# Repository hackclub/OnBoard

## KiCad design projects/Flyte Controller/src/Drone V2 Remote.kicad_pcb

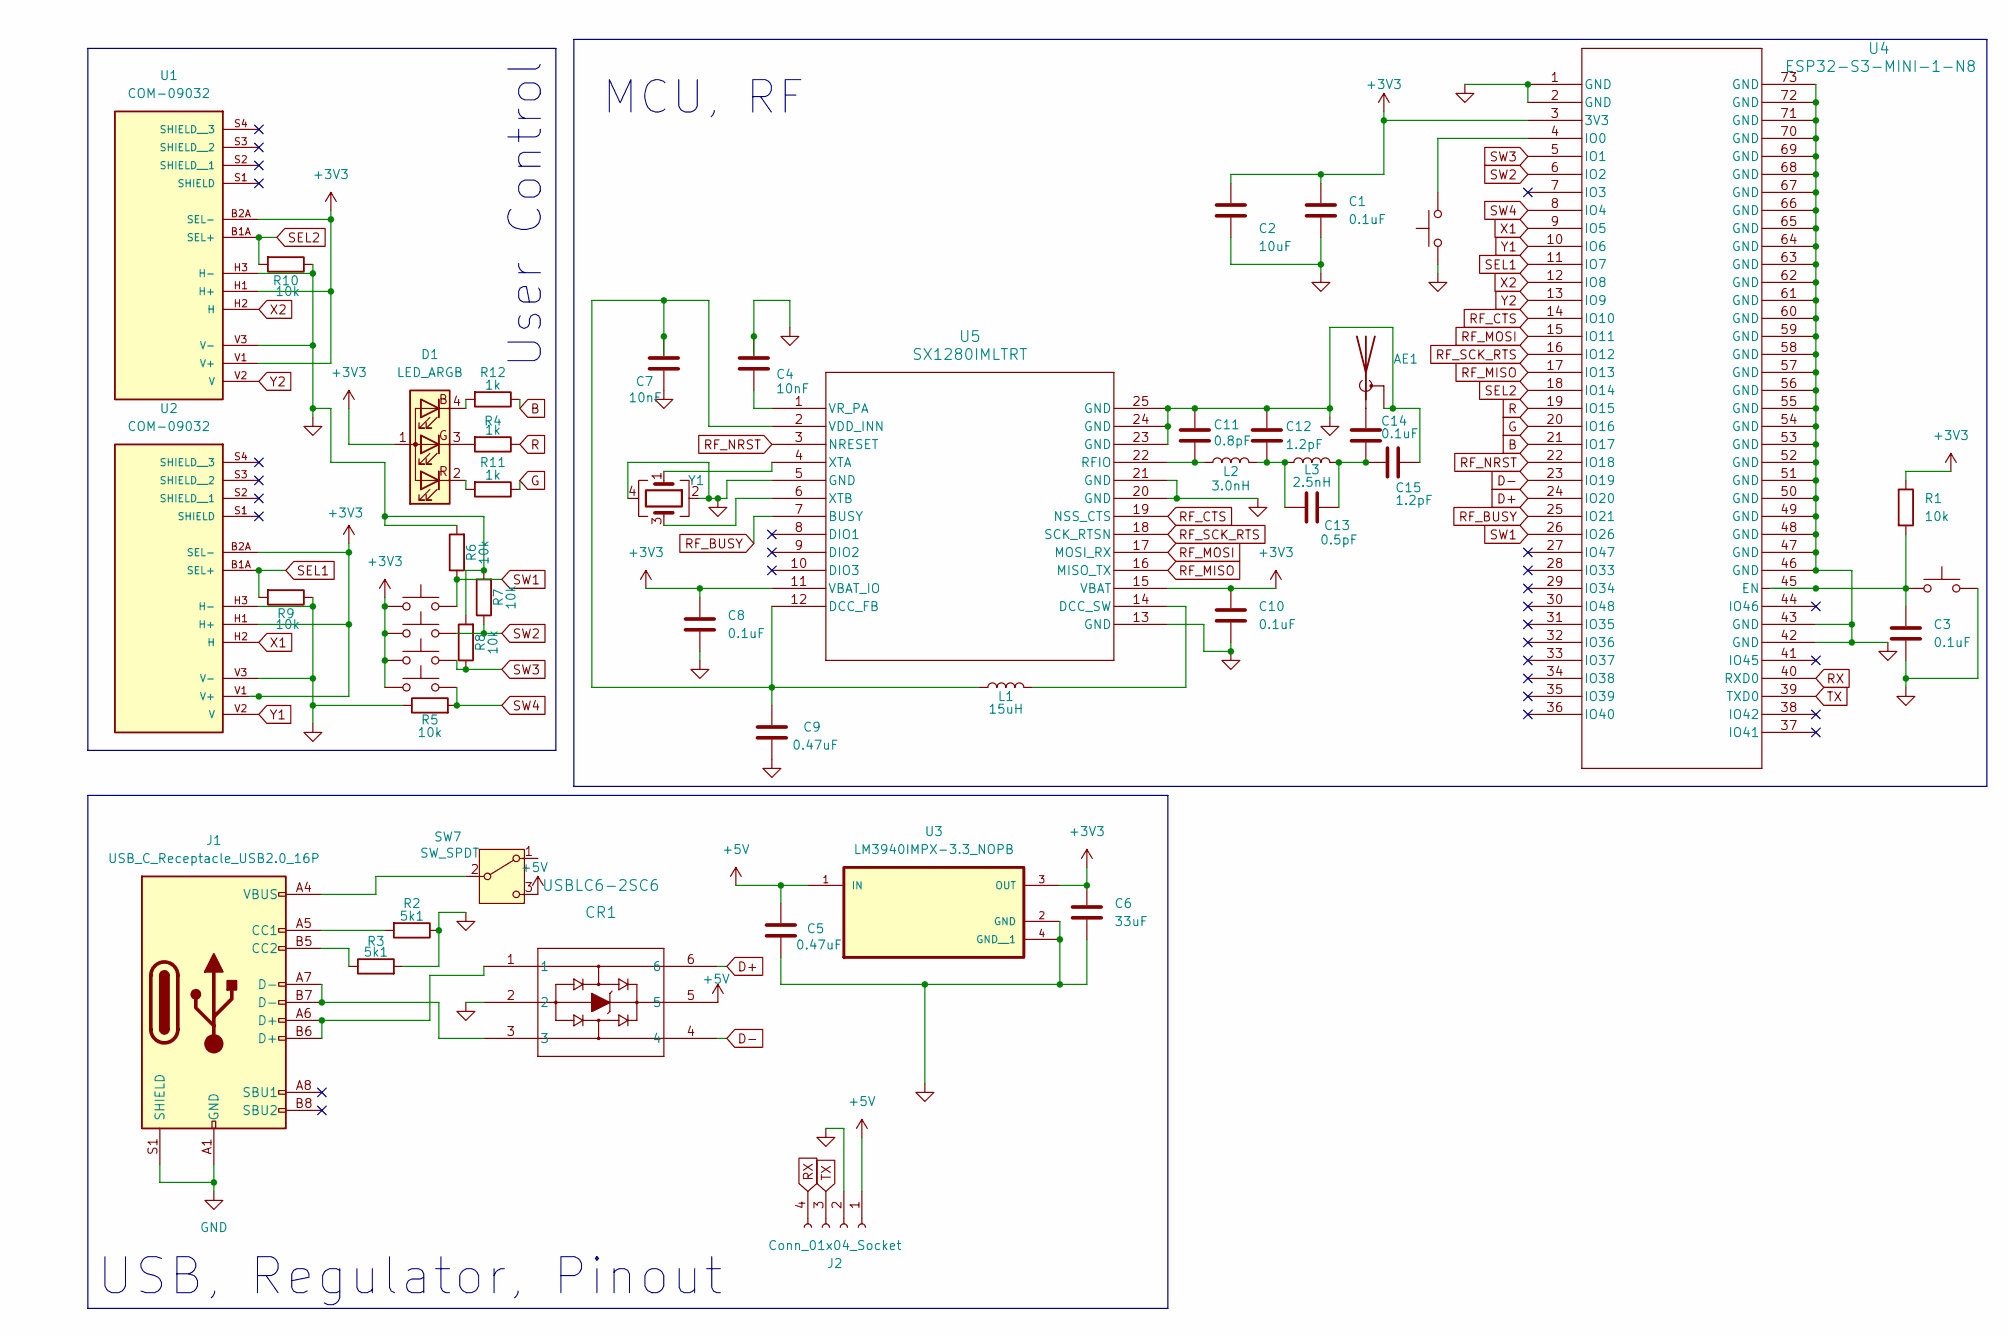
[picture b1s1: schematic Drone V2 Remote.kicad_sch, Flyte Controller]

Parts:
AE1: Antenna_Shield; CINCH_142-0701-801
C1, C3, C8, C10, C14: 0.1uF; CAPC0402X22N
C2: 10uF; CAPC1005X70N
C4, C7: 10nF; CAPC1005X70N
C5, C9: 0.47uF; CAP_CL05_SAM
C6: 33uF; CAP_C1005_TDK
C11: 0.8pF; G-155_MUR
C12, C15: 1.2pF; G-155_MUR
C13: 0.5pF; CAPC1005X55N
CR1: USBLC6-2SC6; SOT23-6L_STM
D1: LED_ARGB; LED_TATRGB_INL
J1: USB_C_Receptacle_USB2.0_16P; USB_C_Receptacle_GCT_USB4105-xx-A_16P_TopMnt_Horizontal
J2: Conn_01x04_Socket; PinHeader_1x04_P1.00mm_Horizontal
L1: 15uH; IND_2012_TDK
L2: 3.0nH; IND1005_LQW15_MUR
L3: 2.5nH; INDC1006X60N
R1, R5, R6, R7, R8, R9, R10: 10k; RC0402N_YAG
R2, R3: 5k1; RES_TNPW0402_VIS
R4, R11, R12: 1k; RC0402N_YAG
SW1, SW2, SW3, SW4: SW_Push; SW_PUSH_6mm_H4.3mm
SW5, SW6: SW_Push; SW_Tactile_SPST_NO_Straight_CK_PTS636Sx25SMTRLFS
SW7: SW_SPDT; SW_EG1218
U1, U2: COM-09032; XDCR_COM-09032; PARTREV N/A
U3: LM3940IMPX-3.3_NOPB; SOT230P700X180-4N
U4: ESP32-S3-MINI-1-N8; ESP32-S3-MINI-1_EXP
U5: SX1280IMLTRT; QFN24_4X4_SEM
Y1: FW520WFMT1; CRYSTAL_FW520WFMT1_DIO

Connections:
+3V3: C1.1, C2.1, C6.1, C8.1, C10.1, D1.1 (A), R1.1, SW1.1, SW2.1, SW3.1, SW4.1, U1.B2A (SEL-), U1.H1 (H+), U1.V1 (V+), U2.B2A (SEL-), U2.H1 (H+), U2.V1 (V+), U3.3 (OUT), U4.3 (3V3), U5.11 (VBAT_IO), U5.15 (VBAT)
+5V: C5.1, CR1.5, J2.1, SW7.3 (C), U3.1 (IN)
B: R12.1, U4.21 (IO17)
D+: CR1.6, U4.24 (IO20)
D-: CR1.4, U4.23 (IO19)
G: R11.1, U4.20 (IO16)
GND: AE1.2 (Shield), C1.2, C2.2, C3.2, C4.1, C5.2, C6.2, C7.2, C8.2, C9.2, C10.2, C11.1, C12.1, C15.1, CR1.2, J1.A1 (GND), J1.A12 (GND), J1.B1 (GND), J1.B12 (GND), J1.S1 (SHIELD), J2.2, R2.1, R3.2, R5.1, R6.2, R7.2, R8.2, R9.1, R10.1, SW5.2, SW6.1, U1.H3 (H-), U1.V3 (V-), U2.H3 (H-), U2.V3 (V-), U3.2 (GND), U3.4 (GND__1), U4.1 (GND), U4.2 (GND), U4.42 (GND), U4.43 (GND), U4.46 (GND), U4.47 (GND), U4.48 (GND), U4.49 (GND), U4.50 (GND), U4.51 (GND), U4.52 (GND), U4.53 (GND), U4.54 (GND), U4.55 (GND), U4.56 (GND), U4.57 (GND), U4.58 (GND), U4.59 (GND), U4.60 (GND), U4.61 (GND), U4.62 (GND), U4.63 (GND), U4.64 (GND), U4.65 (GND), U4.66 (GND), U4.67 (GND), U4.68 (GND), U4.69 (GND), U4.70 (GND), U4.71 (GND), U4.72 (GND), U4.73 (GND), U5.5 (GND), U5.13 (GND), U5.20 (GND), U5.21 (GND), U5.23 (GND), U5.24 (GND), U5.25 (GND), Y1.2, Y1.4
unnamed: AE1.1 (A), C14.1
unnamed: C12.2, C13.1, L2.2, L3.1
unnamed: C13.2, C14.2, C15.2, L3.2
unnamed: CR1.1, J1.A6 (D+), J1.B6 (D+)
unnamed: CR1.3, J1.A7 (D-), J1.B7 (D-)
unnamed: D1.4 (BK), R12.2
unnamed: D1.3 (GK), R4.2
unnamed: D1.2 (RK), R11.2
unnamed: J1.A5 (CC1), R2.2
unnamed: J1.B5 (CC2), R3.1
unnamed: J1.A4 (VBUS), J1.A9 (VBUS), J1.B4 (VBUS), J1.B9 (VBUS), SW7.2 (B)
unnamed: C3.1, R1.2, SW5.1, U4.45 (EN)
unnamed: SW6.2, U4.4 (IO0)
unnamed: C7.1, C9.1, L1.1, U5.2 (VDD_INN), U5.12 (DCC_FB)
unnamed: L1.2, U5.14 (DCC_SW)
unnamed: C11.2, L2.1, U5.22 (RFIO)
unnamed: C4.2, U5.1 (VR_PA)
unnamed: U5.4 (XTA), Y1.1
unnamed: U5.6 (XTB), Y1.3
R: R4.1, U4.19 (IO15)
RF_BUSY: U4.25 (IO21), U5.7 (BUSY)
RF_CTS: U4.14 (IO10), U5.19 (NSS_CTS)
RF_MISO: U4.17 (IO13), U5.16 (MISO_TX)
RF_MOSI: U4.15 (IO11), U5.17 (MOSI_RX)
RF_NRST: U4.22 (IO18), U5.3 (NRESET)
RF_SCK_RTS: U4.16 (IO12), U5.18 (SCK_RTSN)
RX: J2.4, U4.40 (RXD0)
SEL1: R9.2, U2.B1A (SEL+), U4.11 (IO7)
SEL2: R10.2, U1.B1A (SEL+), U4.18 (IO14)
SW1: R6.1, SW1.2, U4.26 (IO26)
SW2: R7.1, SW2.2, U4.6 (IO2)
SW3: R8.1, SW3.2, U4.5 (IO1)
SW4: R5.2, SW4.2, U4.8 (IO4)
TX: J2.3, U4.39 (TXD0)
X1: U2.H2 (H), U4.9 (IO5)
X2: U1.H2 (H), U4.12 (IO8)
Y1: U2.V2 (V), U4.10 (IO6)
Y2: U1.V2 (V), U4.13 (IO9)

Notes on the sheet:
User Control
MCU, RF
USB, Regulator, Pinout

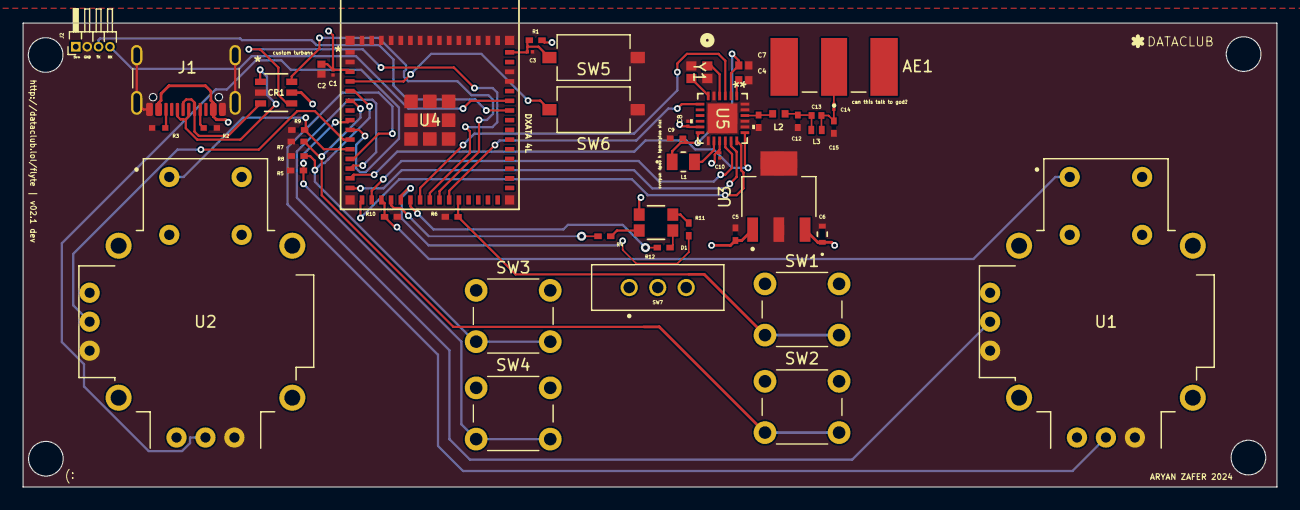
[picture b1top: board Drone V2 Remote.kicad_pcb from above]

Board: 4 copper layers, 110.0 x 40.7 mm, 48 parts (0 on the bottom side), 45 nets.

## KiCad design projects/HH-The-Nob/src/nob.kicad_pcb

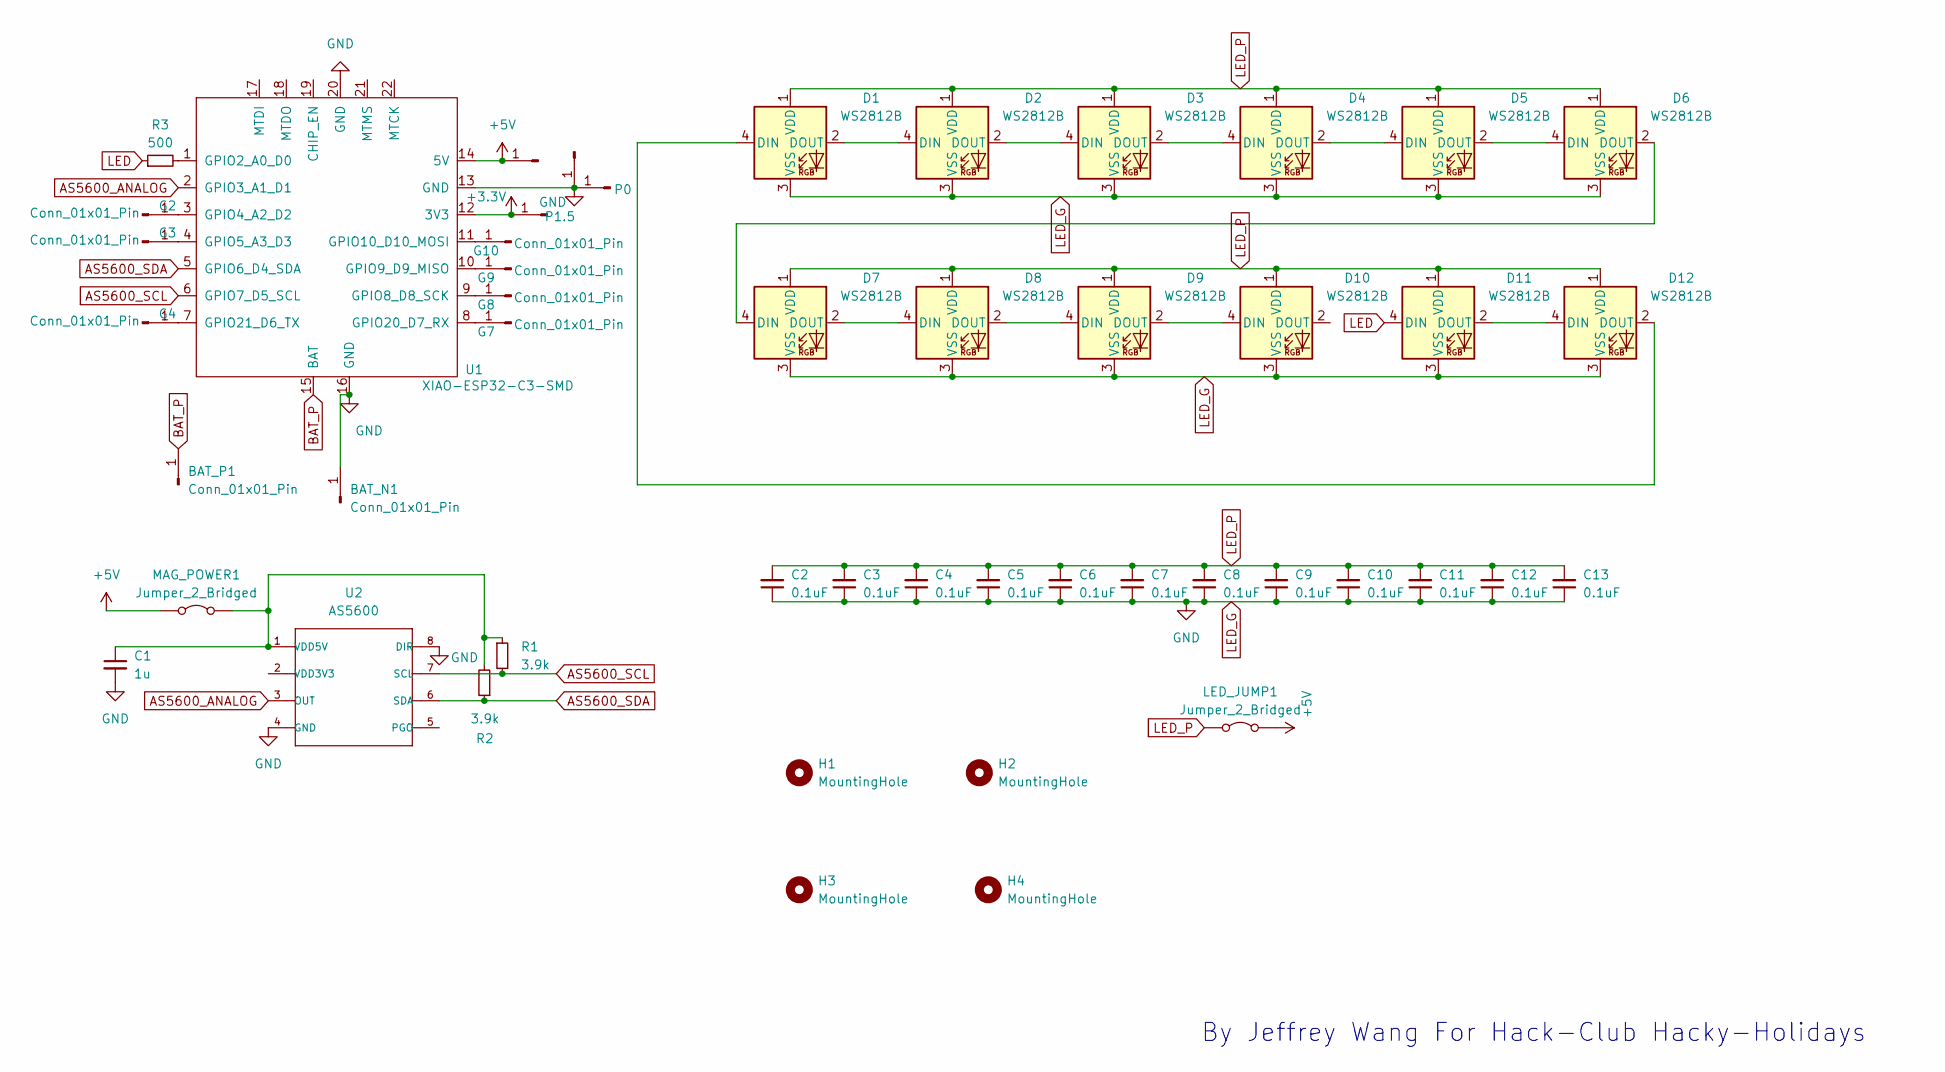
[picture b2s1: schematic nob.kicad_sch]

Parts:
BAT_N1: Conn_01x01_Pin; SolderWire-0.5sqmm_1x01_D0.9mm_OD2.1mm
BAT_P1: Conn_01x01_Pin; SolderWire-0.5sqmm_1x01_D0.9mm_OD2.1mm
C1: 1u; C_0603_1608Metric; LCSC C15849
C2, C3, C4, C5, C6, C7, C8, C9, C10, C11, C12, C13: 0.1uF; C_0805_2012Metric; LCSC C49678
D1, D2, D3, D4, D5, D6, D7, D8, D9, D10, D11, D12: WS2812B; LED_WS2812B_PLCC4_5.0x5.0mm_P3.2mm; LCSC C114586
G2, G3, G4, G7, G8, G9, G10: Conn_01x01_Pin; SolderWire-0.1sqmm_1x01_D0.4mm_OD1mm
H1, H2, H3, H4: MountingHole; MountingHole_3.2mm_M3_DIN965_Pad_TopBottom
LED_JUMP1: Jumper_2_Bridged; SolderJumper-2_P1.3mm_Bridged2Bar_Pad1.0x1.5mm
MAG_POWER1: Jumper_2_Bridged; SolderJumper-2_P1.3mm_Bridged2Bar_Pad1.0x1.5mm
P0, P1, P1.5, P10: Conn_01x01_Pin; SolderWire-0.1sqmm_1x01_D0.4mm_OD1mm
R1, R2: 3.9k; R_0805_2012Metric; LCSC C17614
R3: 500; C_0805_2012Metric; LCSC C17408
U1: XIAO-ESP32-C3-SMD; XIAO-ESP32C3-SMD
U2: AS5600; LCSC C499458

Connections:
+3.3V: P1.5.1, U1.12 (3V3)
+5V: LED_JUMP1.2 (B), MAG_POWER1.1 (A), P1.1, U1.14 (5V)
AS5600_ANALOG: U1.2 (GPIO3_A1_D1), U2.3 (OUT)
AS5600_SCL: R1.2, U1.6 (GPIO7_D5_SCL), U2.7 (SCL)
AS5600_SDA: R2.1, U1.5 (GPIO6_D4_SDA), U2.6 (SDA)
BAT_P: BAT_P1.1, U1.15 (BAT)
LED: D11.4 (DIN), R3.1
LED_G: BAT_N1.1, C1.2, C2.1, C3.1, C4.1, C5.1, C6.1, C7.1, C8.1, C9.1, C10.1, C11.1, C12.1, C13.1, D1.3 (VSS), D2.3 (VSS), D3.3 (VSS), D4.3 (VSS), D5.3 (VSS), D6.3 (VSS), D7.3 (VSS), D8.3 (VSS), D9.3 (VSS), D10.3 (VSS), D11.3 (VSS), D12.3 (VSS), P0.1, P10.1, U1.13 (GND), U1.16 (GND), U1.20 (GND), U2.4 (GND), U2.8 (DIR)
LED_P: C2.2, C3.2, C4.2, C5.2, C6.2, C7.2, C8.2, C9.2, C10.2, C11.2, C12.2, C13.2, D1.1 (VDD), D2.1 (VDD), D3.1 (VDD), D4.1 (VDD), D5.1 (VDD), D6.1 (VDD), D7.1 (VDD), D8.1 (VDD), D9.1 (VDD), D10.1 (VDD), D11.1 (VDD), D12.1 (VDD), LED_JUMP1.1 (A)
unnamed: D1.4 (DIN), D12.2 (DOUT)
unnamed: D1.2 (DOUT), D2.4 (DIN)
unnamed: D2.2 (DOUT), D3.4 (DIN)
unnamed: D3.2 (DOUT), D4.4 (DIN)
unnamed: D4.2 (DOUT), D5.4 (DIN)
unnamed: D5.2 (DOUT), D6.4 (DIN)
unnamed: D6.2 (DOUT), D7.4 (DIN)
unnamed: D7.2 (DOUT), D8.4 (DIN)
unnamed: D8.2 (DOUT), D9.4 (DIN)
unnamed: D9.2 (DOUT), D10.4 (DIN)
unnamed: D11.2 (DOUT), D12.4 (DIN)
unnamed: G2.1, U1.3 (GPIO4_A2_D2)
unnamed: G3.1, U1.4 (GPIO5_A3_D3)
unnamed: G4.1, U1.7 (GPIO21_D6_TX)
unnamed: G7.1, U1.8 (GPIO20_D7_RX)
unnamed: G8.1, U1.9 (GPIO8_D8_SCK)
unnamed: G9.1, U1.10 (GPIO9_D9_MISO)
unnamed: G10.1, U1.11 (GPIO10_D10_MOSI)
unnamed: C1.1, MAG_POWER1.2 (B), R1.1, R2.2, U2.1 (VDD5V)
unnamed: R3.2, U1.1 (GPIO2_A0_D0)

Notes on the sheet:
By Jeffrey Wang For Hack-Club Hacky-Holidays

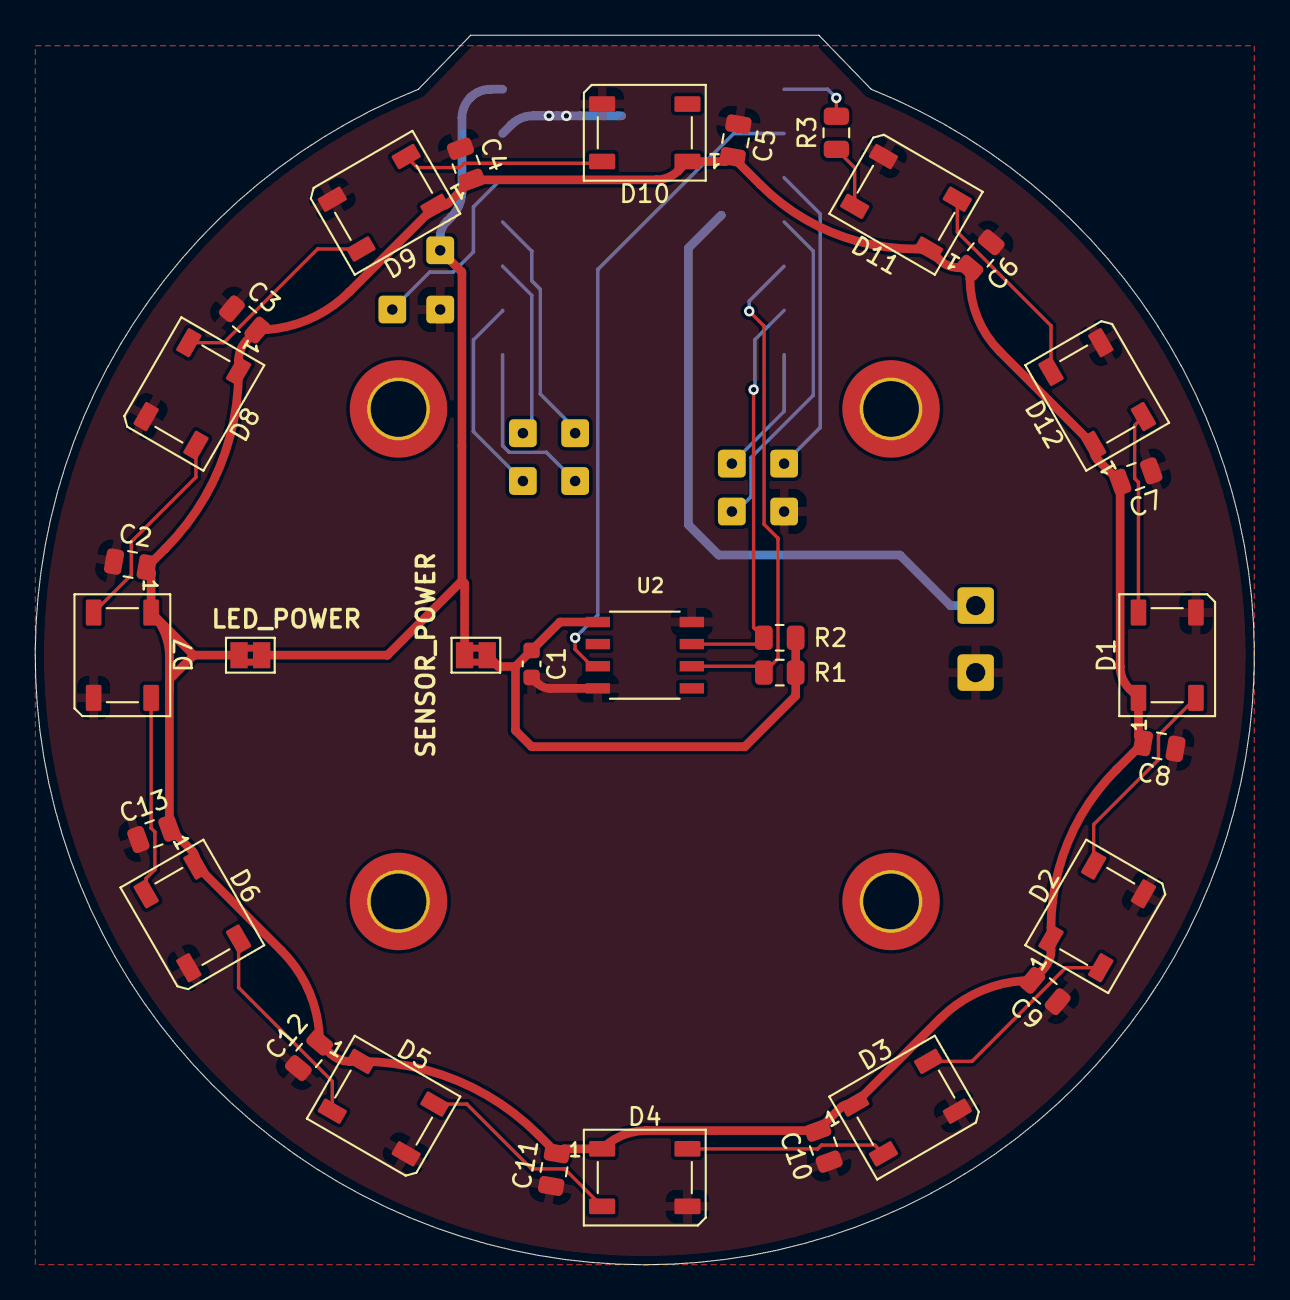
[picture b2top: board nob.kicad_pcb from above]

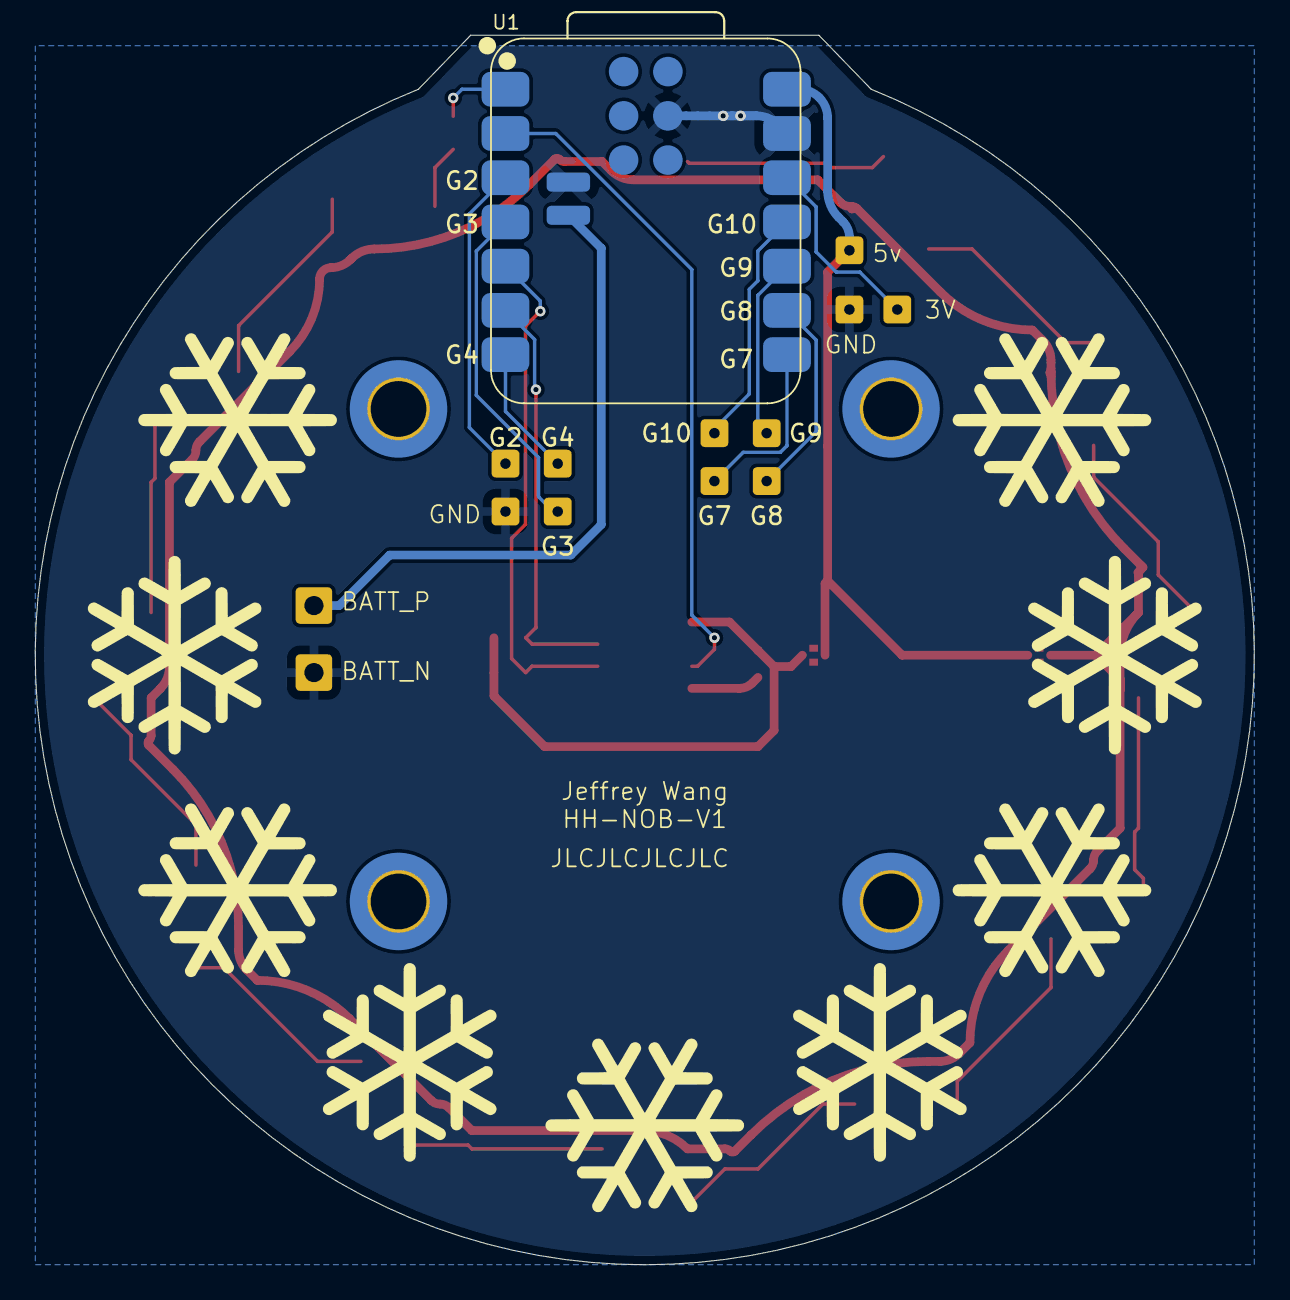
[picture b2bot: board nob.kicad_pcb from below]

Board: 2 copper layers, 70.0 x 70.6 mm, 49 parts (14 on the bottom side), 29 nets.

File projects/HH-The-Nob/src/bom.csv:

Designator,Footprint,Quantity,Value,LCSC Part #
"BAT_N1, BAT_P1",SolderWire-0.5sqmm_1x01_D0.9mm_OD2.1mm,2,Conn_01x01_Pin,
C1,0603,1,1u,C15849
"C10, C11, C12, C13, C2, C3, C4, C5, C6, C7, C8, C9",0805,12,0.1uF,C49678
"D1, D10, D11, D12, D2, D3, D4, D5, D6, D7, D8, D9",LED_WS2812B_PLCC4_5.0x5.0mm_P3.2mm,12,WS2812B,C114586
"G10, G2, G3, G4, G7, G8, G9, P0, P1, P1.5, P10",SolderWire-0.1sqmm_1x01_D0.4mm_OD1mm,11,Conn_01x01_Pin,
"LED_JUMP1, MAG_POWER1",SolderJumper-2_P1.3mm_Bridged2Bar_Pad1.0x1.5mm,2,Jumper_2_Bridged,
"R1, R2",0805,2,3.9k,C17614
R3,0805,1,500,C17408
U1,XIAO-ESP32C3-SMD,1,XIAO-ESP32-C3-SMD,
U2,AS5600,1,AS5600,C499458

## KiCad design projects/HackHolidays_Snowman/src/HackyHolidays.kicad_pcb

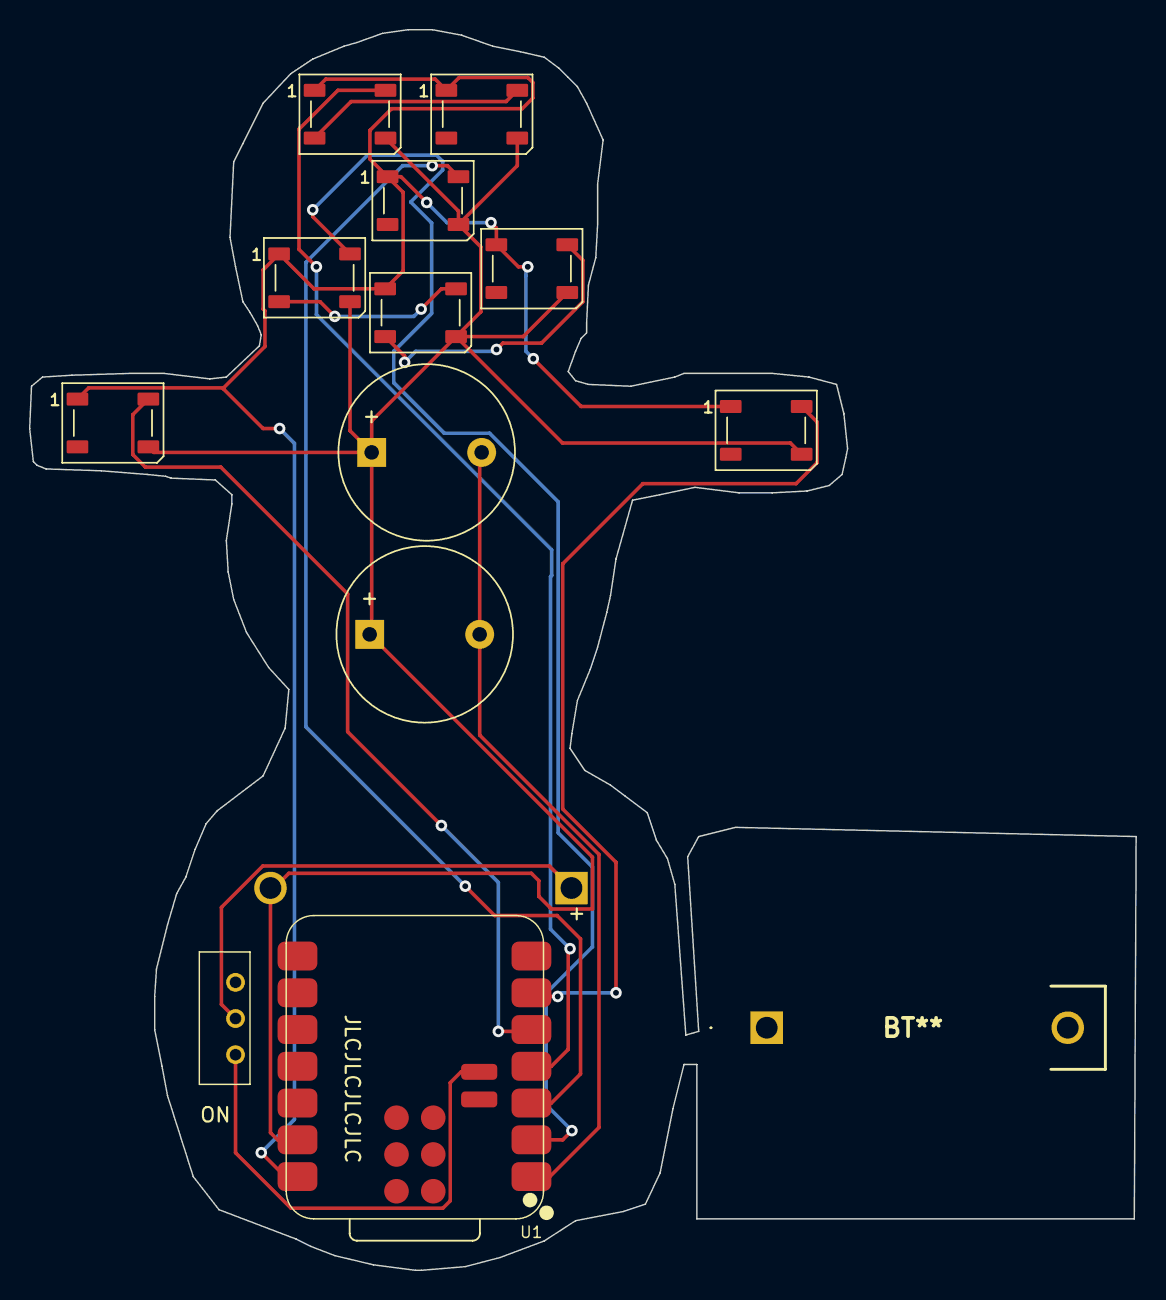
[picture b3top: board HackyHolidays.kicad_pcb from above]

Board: 2 copper layers, 76.5 x 85.7 mm, 14 parts (1 on the bottom side), 13 nets.

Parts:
BT1: BS-07-A1BJ001; K31260DL1
BT**: BS07A1BJ001
BZ1, BZ2: Buzzer; Buzzer_12x9.5RM7.6
D1, D2, D3, D8, D10, D11, D12, D13: WS2812B; LED_WS2812B_PLCC4_5.0x5.0mm_P3.2mm
S1: K3-1260D-L1; BS07A1BJ001
U1: XIAO-ESP32-C3-SMD; XIAO-ESP32C3-SMD

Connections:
+5V: D1.1 (VDD), D2.1 (VDD), D3.1 (VDD), D8.1 (VDD), D10.1 (VDD), D11.1 (VDD), D12.1 (VDD), D13.1 (VDD), U1.14 (5V)
GND: BZ1.1 (+), BZ2.1 (+), D1.3 (VSS), D2.3 (VSS), D3.3 (VSS), D8.3 (VSS), D10.3 (VSS), D11.3 (VSS), D12.3 (VSS), D13.3 (VSS), S1.2, U1.13 (GND)
unnamed: BT1.1 (+), U1.15 (BAT)
unnamed: BT1.2 (-), S1.1
unnamed: BZ1.2 (-), BZ2.2 (-), U1.1 (GPIO2_A0_D0)
unnamed: D1.4 (DIN), U1.3 (GPIO4_A2_D2)
unnamed: D2.4 (DIN), D8.2 (DOUT)
unnamed: D2.2 (DOUT), D3.4 (DIN)
unnamed: D8.4 (DIN), U1.2 (GPIO3_A1_D1)
unnamed: D10.4 (DIN), U1.4 (GPIO5_A3_D3)
unnamed: D10.2 (DOUT), D11.4 (DIN)
unnamed: D12.4 (DIN), U1.5 (GPIO6_D4_SDA)
unnamed: D13.4 (DIN), U1.6 (GPIO7_D5_SCL)

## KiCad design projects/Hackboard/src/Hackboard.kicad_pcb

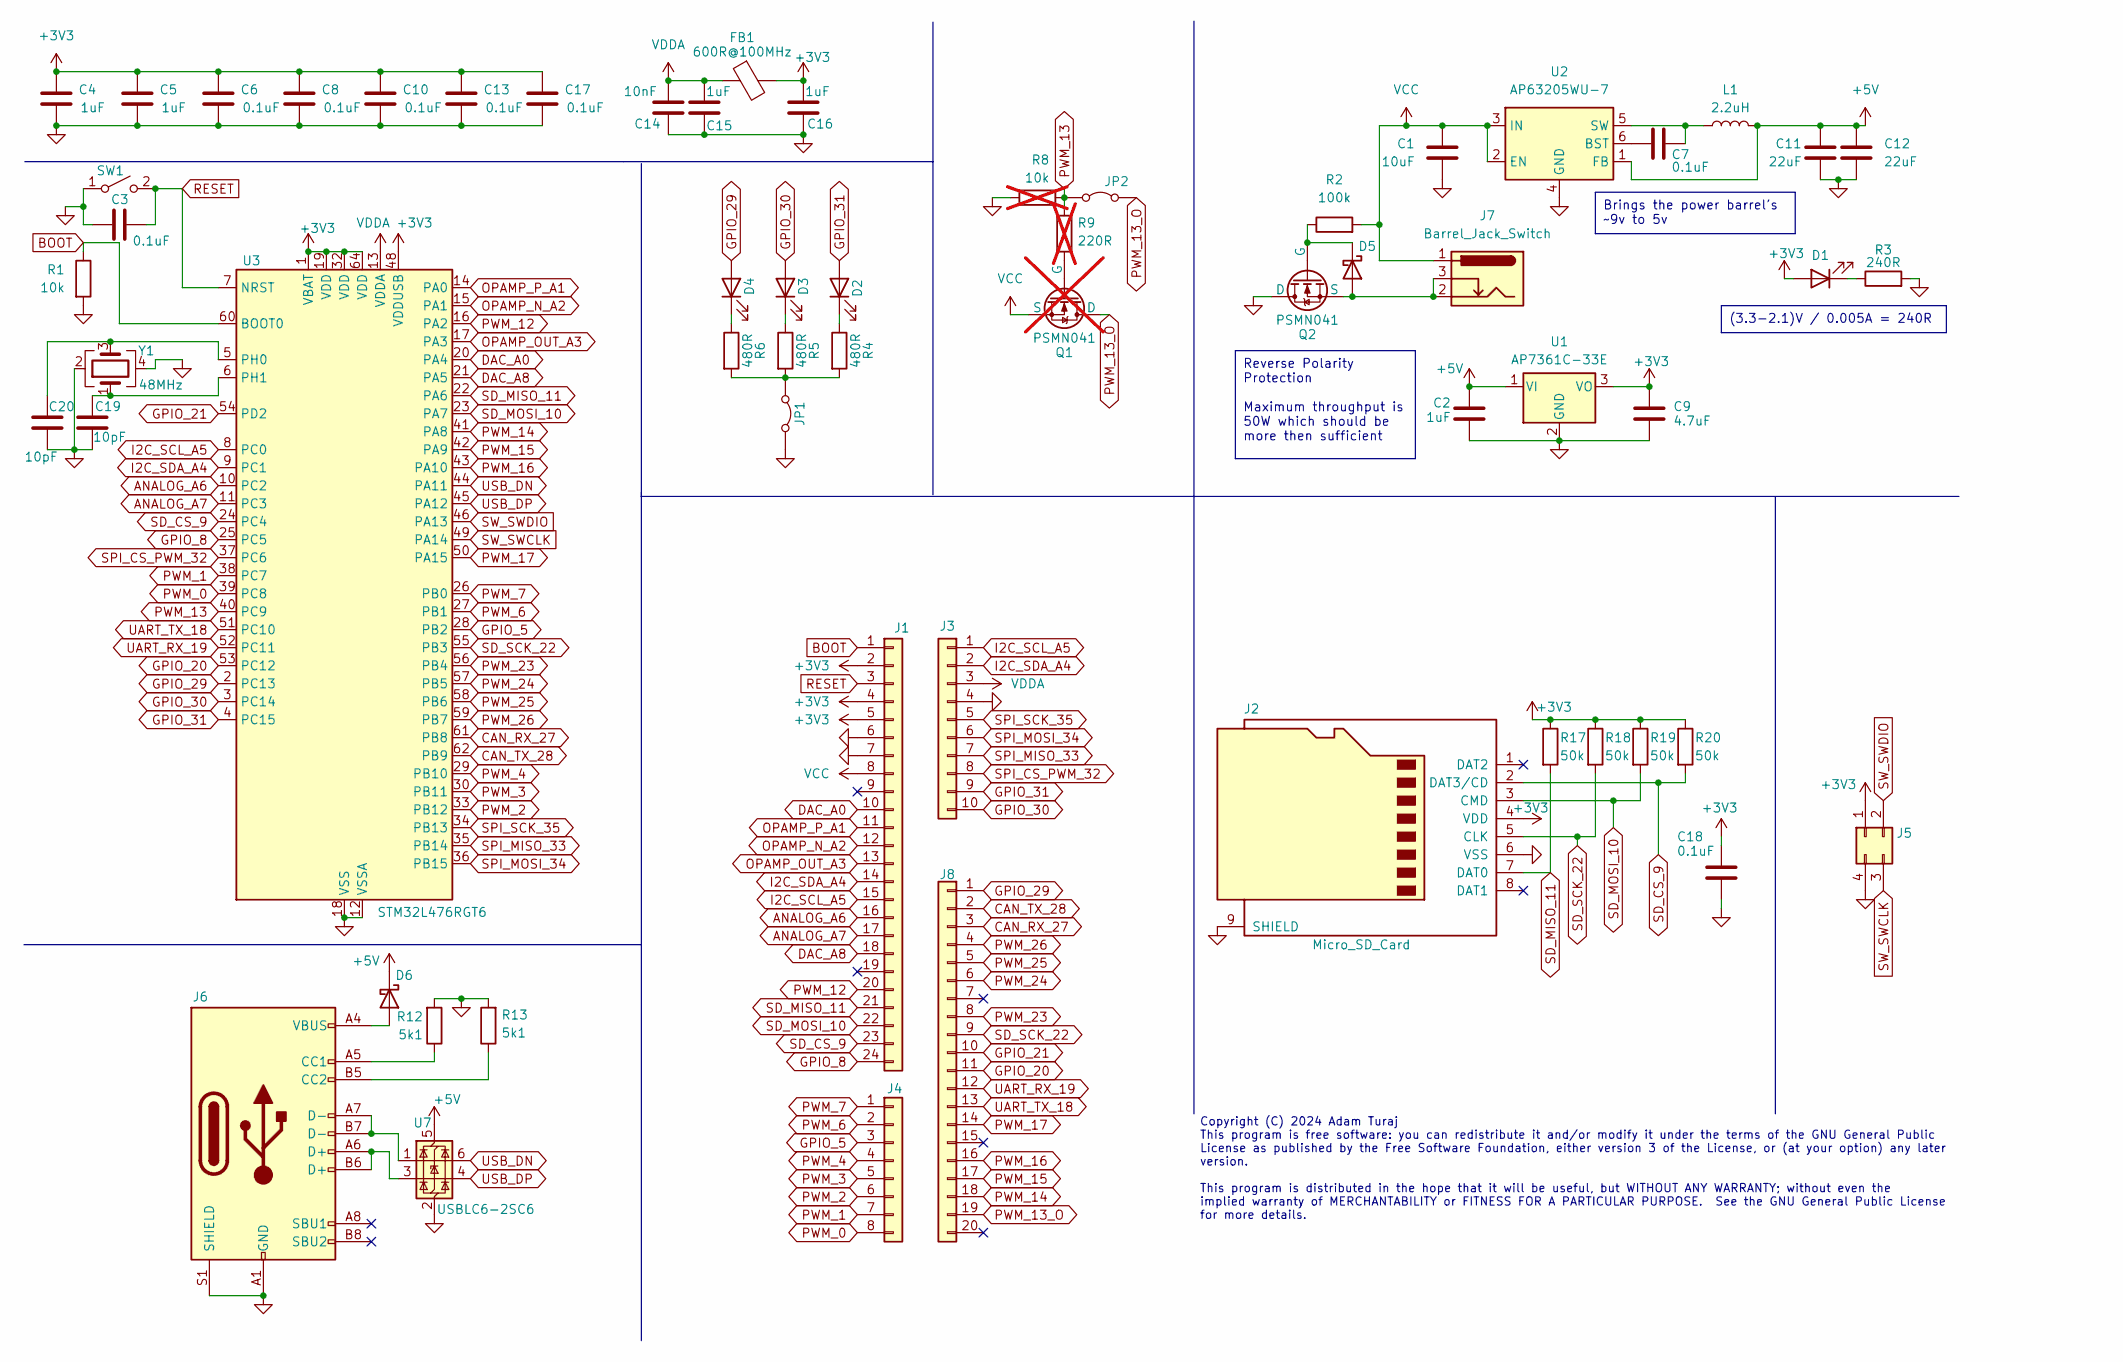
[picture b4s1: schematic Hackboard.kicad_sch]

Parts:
C1: 10uF; C_1206_3216Metric; MPN 0603DD106MAT2A
C2, C4, C5, C15, C16: 1uF; C_0603_1608Metric; MPN CC0603KRX7R7BB105
C3, C6, C7, C8, C10, C13, C17, C18: 0.1uF; C_0603_1608Metric; MPN GCM188R71H104KA57D
C9: 4.7uF; C_0603_1608Metric; MPN AP7361-33E-13
C11, C12: 22uF; C_0603_1608Metric; MPN C1608X5R1A226M080AC
C14: 10nF; C_0603_1608Metric; MPN 0603B103K500CT
C19, C20: 10pF; C_0603_1608Metric; MPN 0603N100J500CT
D1, D3: LED; LED_0603_1608Metric; MPN LTST-C190GKT
D2: LED; LED_0603_1608Metric; MPN LTST-C190TBKT
D4: LED; LED_0603_1608Metric; MPN LTST-C191KRKT
D5, D6: D_Schottky; D_SMB; MPN SSB44-E3/52T
FB1: 600R@100MHz; L_0603_1608Metric; MPN BLM18AG601SN1D
J1: Conn_01x24; PinSocket_1x24_P2.54mm_Vertical; MPN PPTC241LFBN-RC
J2: Micro_SD_Card; CONN9_MSD-1_CUD; MPN MSD-1-A
J3: Conn_01x10; PinSocket_1x10_P2.54mm_Vertical; MPN PPPC101LFBN-RC
J4: Conn_01x08; PinSocket_1x08_P2.54mm_Vertical; MPN 61300811821
J5: Conn_02x02_Counter_Clockwise; PinHeader_2x02_P2.54mm_Vertical
J6: USB_C_Receptacle_USB2.0_16P; USB_C_Receptacle_Amphenol_GSB1C4; MPN GSB1C411111DS1HR
J7: Barrel_Jack_Switch; CUI_PJ-002AH; MPN PJ-002AH
J8: Conn_01x20; PinSocket_1x20_P2.54mm_Vertical; MPN 61302011821
JP1, JP2: Jumper_2_Bridged; SolderJumper-2_P1.3mm_Open_RoundedPad1.0x1.5mm; MPN PPPC022LFBN-RC
L1: 2.2uH; L_Vishay_IFSC-1515AH_4x4x1.8mm; MPN IFSC1515AHER2R2M01
Q1: PSMN041; LFPAK56; MPN PSMN041-80YLX; not fitted
Q2: PSMN041; LFPAK56; MPN PSMN041-80YLX
R1: 10k; R_0603_1608Metric; MPN RMCF0603JT10K0
R2: 100k; R_0603_1608Metric; MPN ERJ-3EKF1003V
R3: 240R; R_0603_1608Metric; MPN CRGCQ0603J220R
R4, R5, R6: 480R; R_0603_1608Metric; MPN CRGCQ0603J220R
R8: 10k; R_0603_1608Metric; MPN RMCF0603JT10K0; not fitted
R9: 220R; R_0603_1608Metric; MPN CRGCQ0603J220R; not fitted
R12, R13: 5k1; R_0603_1608Metric; MPN RC0603FR-075K1L
R17, R18, R19, R20: 50k; R_0603_1608Metric; MPN RT0603BRD0750KL
SW1: SW_SPST; SW_SPST_PTS645; MPN PTS645SK43SMTR92 LFS
U1: AP7361C-33E; SOT-223-3_TabPin2; MPN AP7361C-33E-13
U2: AP63205WU-7; TSOT-23-6; MPN AP63205WU-7
U3: STM32L476RGT6; LQFP-64_10x10mm_P0.5mm; MPN STM32L476RGT6
U7: USBLC6-2SC6; SOT-23-6; MPN USBLC6-2SC6
Y1: 48MHz; Oscillator_SMD_Abracon_ASE-4Pin_3.2x2.5mm; MPN RH100-48.000-8-F-1015-EXT-TR

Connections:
+3V3: C4.1, C5.1, C6.1, C8.1, C9.2, C10.1, C13.1, C16.2, C17.1, C18.1, D1.2 (A), FB1.2, J1.2, J1.4, J1.5, J2.4 (VDD), J5.1, R17.1, R18.1, R19.1, R20.1, U1.3 (VO), U3.1 (VBAT), U3.19 (VDD), U3.32 (VDD), U3.48 (VDDUSB), U3.64 (VDD)
+5V: C2.1, C11.1, C12.1, D6.1 (K), L1.2, U1.1 (VI), U2.1 (FB), U7.5 (VBUS)
ANALOG_A6: J1.16, U3.10 (PC2)
ANALOG_A7: J1.17, U3.11 (PC3)
BOOT: J1.1, R1.1, U3.60 (BOOT0)
CAN_RX_27: J8.3, U3.61 (PB8)
CAN_TX_28: J8.2, U3.62 (PB9)
DAC_A0: J1.10, U3.20 (PA4)
DAC_A8: J1.18, U3.21 (PA5)
GND: C1.2, C2.2, C3.2, C4.2, C5.2, C6.2, C8.2, C9.1, C10.2, C11.2, C12.2, C13.2, C14.1, C15.1, C16.1, C17.2, C18.2, C19.2, C20.2, J1.6, J1.7, J2.6 (VSS), J2.9 (SHIELD), J3.4, J5.4, J6.A1 (GND), J6.A12 (GND), J6.B1 (GND), J6.B12 (GND), J6.S1 (SHIELD), JP1.1 (A), Q2.1 (D), R1.2, R3.2, R8.2, R12.2, R13.2, SW1.1 (A), U1.2 (GND), U2.4 (GND), U3.12 (VSSA), U3.18 (VSS), U3.31 (VSS), U3.47 (VSS), U3.63 (VSS), U7.2 (GND), Y1.2, Y1.4
GPIO_5: J4.3, U3.28 (PB2)
GPIO_8: J1.24, U3.25 (PC5)
GPIO_20: J8.11, U3.53 (PC12)
GPIO_21: J8.10, U3.54 (PD2)
GPIO_29: D4.2 (A), J8.1, U3.2 (PC13)
GPIO_30: D3.2 (A), J3.10, U3.3 (PC14)
GPIO_31: D2.2 (A), J3.9, U3.4 (PC15)
I2C_SCL_A5: J1.15, J3.1, U3.8 (PC0)
I2C_SDA_A4: J1.14, J3.2, U3.9 (PC1)
unnamed: D1.1 (K), R3.1
unnamed: D2.1 (K), R4.1
unnamed: D3.1 (K), R5.1
unnamed: D4.1 (K), R6.1
unnamed: D5.2 (A), J7.2, J7.3, Q2.3 (S)
unnamed: D5.1 (K), Q2.2 (G), R2.1
unnamed: D6.2 (A), J6.A4 (VBUS), J6.A9 (VBUS), J6.B4 (VBUS), J6.B9 (VBUS)
unnamed: J6.A5 (CC1), R12.1
unnamed: J6.B5 (CC2), R13.1
unnamed: J6.A6 (D+), J6.B6 (D+), U7.3 (I/O2)
unnamed: J6.A7 (D-), J6.B7 (D-), U7.1 (I/O1)
unnamed: JP1.2 (B), R4.2, R5.2, R6.2
unnamed: Q1.2 (G), R9.1
unnamed: C7.1, U2.6 (BST)
unnamed: C7.2, L1.1, U2.5 (SW)
unnamed: C20.1, U3.5 (PH0), Y1.3
unnamed: C19.1, U3.6 (PH1), Y1.1
OPAMP_N_A2: J1.12, U3.15 (PA1)
OPAMP_OUT_A3: J1.13, U3.17 (PA3)
OPAMP_P_A1: J1.11, U3.14 (PA0)
PWM_0: J4.8, U3.39 (PC8)
PWM_1: J4.7, U3.38 (PC7)
PWM_2: J4.6, U3.33 (PB12)
PWM_3: J4.5, U3.30 (PB11)
PWM_4: J4.4, U3.29 (PB10)
PWM_6: J4.2, U3.27 (PB1)
PWM_7: J4.1, U3.26 (PB0)
PWM_12: J1.20, U3.16 (PA2)
PWM_13: JP2.1 (A), R8.1, R9.2, U3.40 (PC9)
PWM_13_O: J8.19, JP2.2 (B), Q1.1 (D)
PWM_14: J8.18, U3.41 (PA8)
PWM_15: J8.17, U3.42 (PA9)
PWM_16: J8.16, U3.43 (PA10)
PWM_17: J8.14, U3.50 (PA15)
PWM_23: J8.8, U3.56 (PB4)
PWM_24: J8.6, U3.57 (PB5)
PWM_25: J8.5, U3.58 (PB6)
PWM_26: J8.4, U3.59 (PB7)
RESET: C3.1, J1.3, SW1.2 (B), U3.7 (NRST)
SD_CS_9: J1.23, J2.2 (DAT3/CD), R20.2, U3.24 (PC4)
SD_MISO_11: J1.21, J2.7 (DAT0), R17.2, U3.22 (PA6)
SD_MOSI_10: J1.22, J2.3 (CMD), R19.2, U3.23 (PA7)
SD_SCK_22: J2.5 (CLK), J8.9, R18.2, U3.55 (PB3)
SPI_CS_PWM_32: J3.8, U3.37 (PC6)
SPI_MISO_33: J3.7, U3.35 (PB14)
SPI_MOSI_34: J3.6, U3.36 (PB15)
SPI_SCK_35: J3.5, U3.34 (PB13)
SW_SWCLK: J5.3, U3.49 (PA14)
SW_SWDIO: J5.2, U3.46 (PA13)
UART_RX_19: J8.12, U3.52 (PC11)
UART_TX_18: J8.13, U3.51 (PC10)
USB_DN: U3.44 (PA11), U7.6 (I/O1)
USB_DP: U3.45 (PA12), U7.4 (I/O2)
VCC: C1.1, J1.8, J7.1, Q1.3 (S), R2.2, U2.2 (EN), U2.3 (IN)
VDDA: C14.2, C15.2, FB1.1, J3.3, U3.13 (VDDA)

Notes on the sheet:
Brings the power barrel's ~9v to 5v
Reverse Polarity Protection Maximum throughput is 50W which should be more then sufficient
(3.3-2.1)V / 0.005A = 240R
Copyright (C) 2024 Adam Turaj This program is free software: you can redistribute it and/or modify it under the terms of the GNU General Public License as published by the Free Software Foundation, either version 3 of the License, or (at your option) any later version. This program is distributed i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

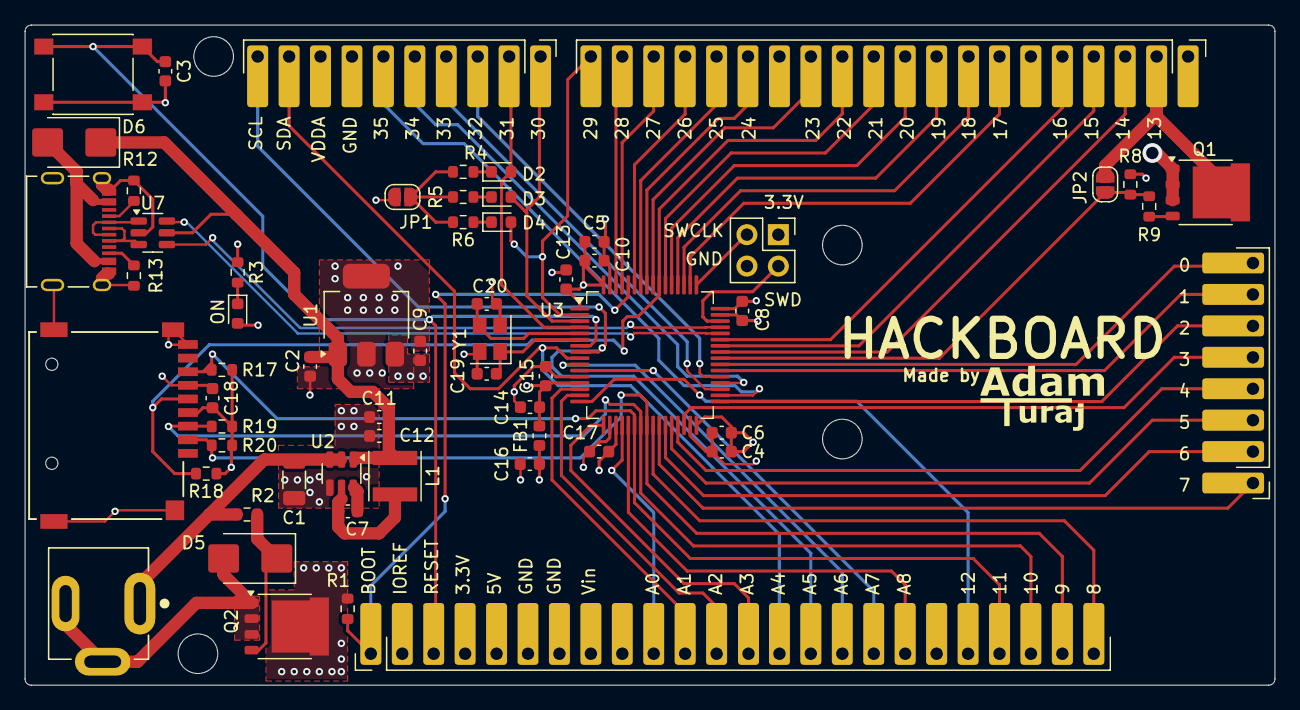
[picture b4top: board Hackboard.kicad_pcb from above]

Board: 4 copper layers, 101.0 x 53.3 mm, 64 parts (0 on the bottom side), 74 nets.

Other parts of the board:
H1, H2, H3, H4: MountingHole; MountingHole_3.2mm_M3
